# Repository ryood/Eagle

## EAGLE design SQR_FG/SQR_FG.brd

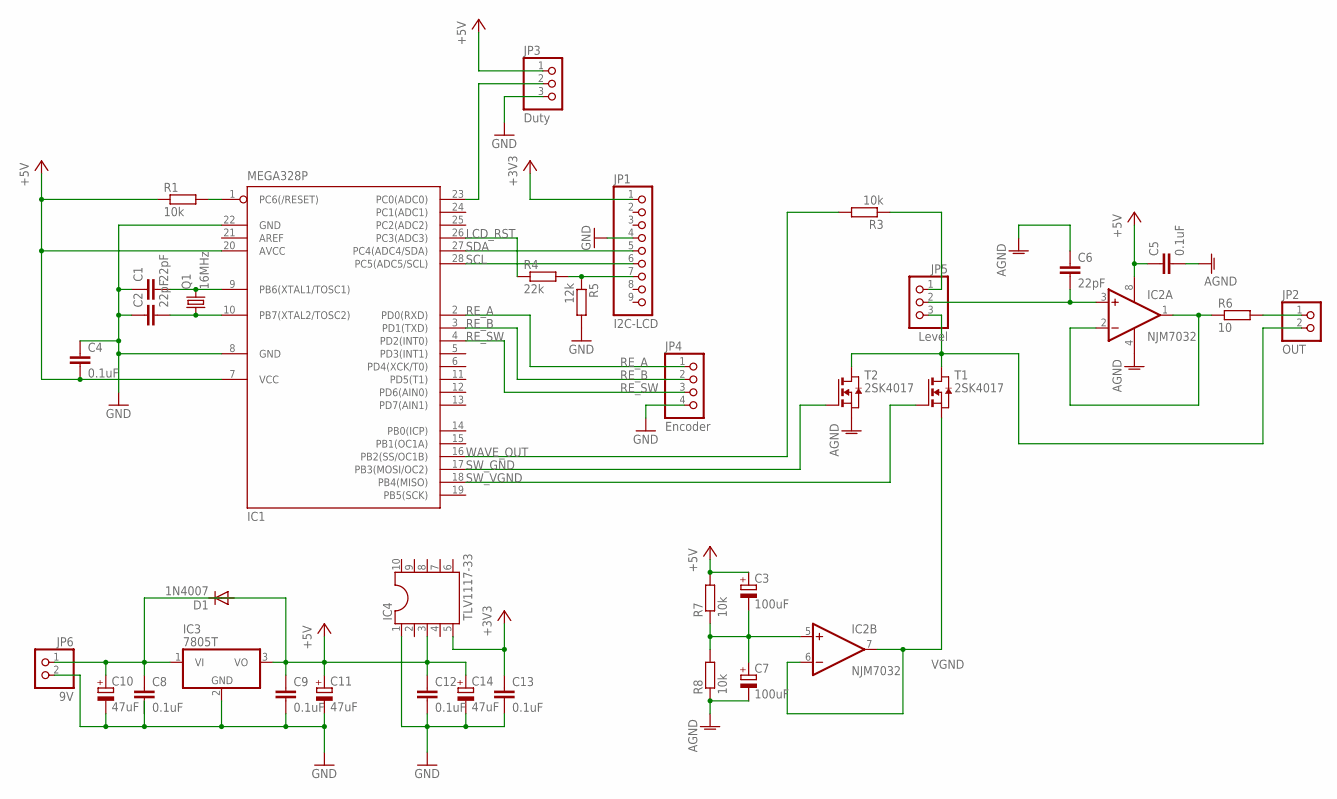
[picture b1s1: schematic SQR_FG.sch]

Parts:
C1, C2, C6: 22pF; C025-024X044
C3, C7: 100uF; E2,5-5
C4, C5, C8, C9, C12, C13: 0.1uF; C025-024X044
C10, C11, C14: 47uF; TT2D5L
D1: 1N4007; DO41-10
IC1: MEGA328P; DIL28-3
IC2: NJM7032; DIL08
IC3: 7805T; TO220H
IC4: TLV1117-33; DIL10
JP1: I2C-LCD; 1X09
JP2: OUT; 1X02
JP3: Duty; 1X03
JP4: Encoder; 1X04
JP5: Level; 1X03
JP6: 9V; 1X02
Q1: 16MHz; HC49/S
R1, R3, R7, R8: 10k; 0207/7
R4: 22k; 0207/7
R5: 12k; 0207/7
R6: 10; 0207/7
T1, T2: 2SK4017; E3LINE

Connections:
+3V3: C13.1, IC4.5, JP1.1
+5V: C3.+, C4.2, C5.1, C8.1, C9.1, C10.+, C11.+, C12.1, C14.+, IC1.7 (VCC), IC1.20 (AVCC), IC2.8 (V+), IC3.1 (VI), IC3.3 (VO), IC4.3, JP3.1, JP6.1, R1.1, R7.2
AGND: C5.2, C6.1, C7.-, IC2.4 (V-), R8.1, T2.3 (S)
GND: C1.1, C2.1, C4.1, C8.2, C9.2, C10.-, C11.-, C12.2, C13.2, C14.-, IC1.8 (GND), IC1.22 (GND), IC3.2 (GND), IC4.1, JP1.4, JP3.3, JP4.4, JP6.2, R5.2
LCD_RST: IC1.26 (PC3(ADC3)), R4.1
unnamed: C1.2, IC1.9 (PB6(XTAL1/TOSC1)), Q1.2
unnamed: C2.2, IC1.10 (PB7(XTAL2/TOSC2)), Q1.1
unnamed: IC1.1 (PC6(/RESET)), R1.2
unnamed: JP2.2, JP5.3, T1.1 (D), T2.1 (D)
unnamed: JP5.1, R3.1
unnamed: IC1.23 (PC0(ADC0)), JP3.2
unnamed: JP2.1, R6.2
unnamed: C6.2, IC2.3 (+IN), JP5.2
unnamed: IC2.1 (OUT), IC2.2 (-IN), R6.1
unnamed: C3.-, C7.+, IC2.5 (+IN), R7.1, R8.2
RE_A: IC1.2 (PD0(RXD)), JP4.1
RE_B: IC1.3 (PD1(TXD)), JP4.2
RE_SW: IC1.4 (PD2(INT0)), JP4.3
RST: JP1.7, R4.2, R5.1
SCL: IC1.28 (PC5(ADC5/SCL)), JP1.6
SDA: IC1.27 (PC4(ADC4/SDA)), JP1.5
SW_GND: IC1.17 (PB3(MOSI/OC2)), T2.2 (G)
SW_VGND: IC1.18 (PB4(MISO)), T1.2 (G)
VGND: IC2.6 (-IN), IC2.7 (OUT), T1.3 (S)
WAVE_OUT: IC1.16 (PB2(SS/OC1B)), R3.2

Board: 2 copper layers, 35 parts (0 on the bottom side), 25 nets, no tracks yet.

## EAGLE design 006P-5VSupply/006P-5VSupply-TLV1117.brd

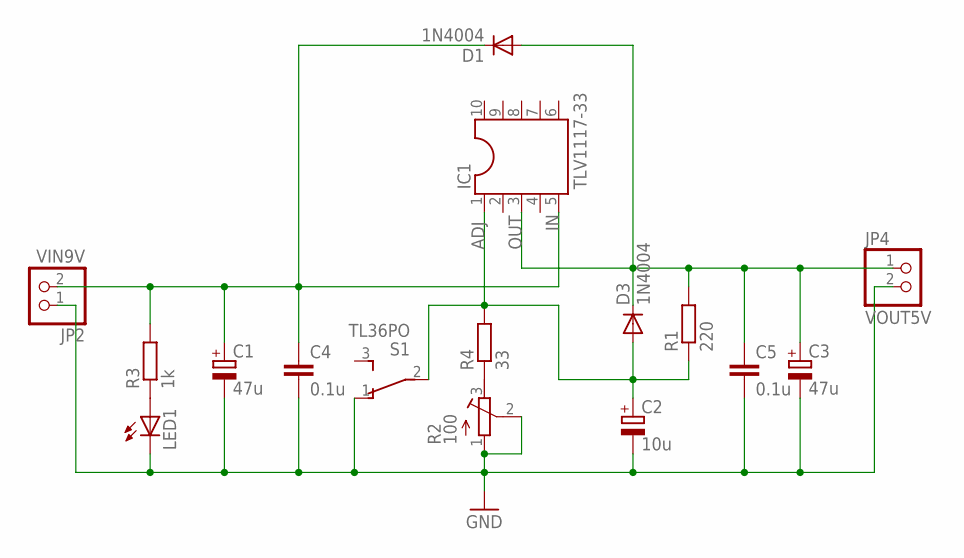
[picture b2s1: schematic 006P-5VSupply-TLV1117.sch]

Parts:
C1, C3: 47u; E2-4
C2: 10u; E2-4
C4, C5: 0.1u; C025-024X044
D1, D3: 1N4004; DO41-10
IC1: TLV1117-33; DIL10
JP2: VIN9V; 1X02
JP4: VOUT5V; 1X02
LED1: LED3MM
R1: 220; 0207/7
R2: 100; RTRIM3339P
R3: 1k; 0207/7
R4: 33; 0207/7
S1: TL36PO; TL3XPO

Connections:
ADJ: C2.+, D3.A, IC1.1, R1.1, R4.2, S1.2
GND: C1.-, C2.-, C3.-, C4.2, C5.2, JP2.1, JP4.2, LED1.K (C), R2.1 (A), R2.2 (S), S1.1 (O)
IN: C1.+, C4.1, D1.C, IC1.5, JP2.2, R3.2
unnamed: R2.3 (E), R4.1
unnamed: LED1.A, R3.1
OUT: C3.+, C5.1, D1.A, D3.C, IC1.3, JP4.1, R1.2

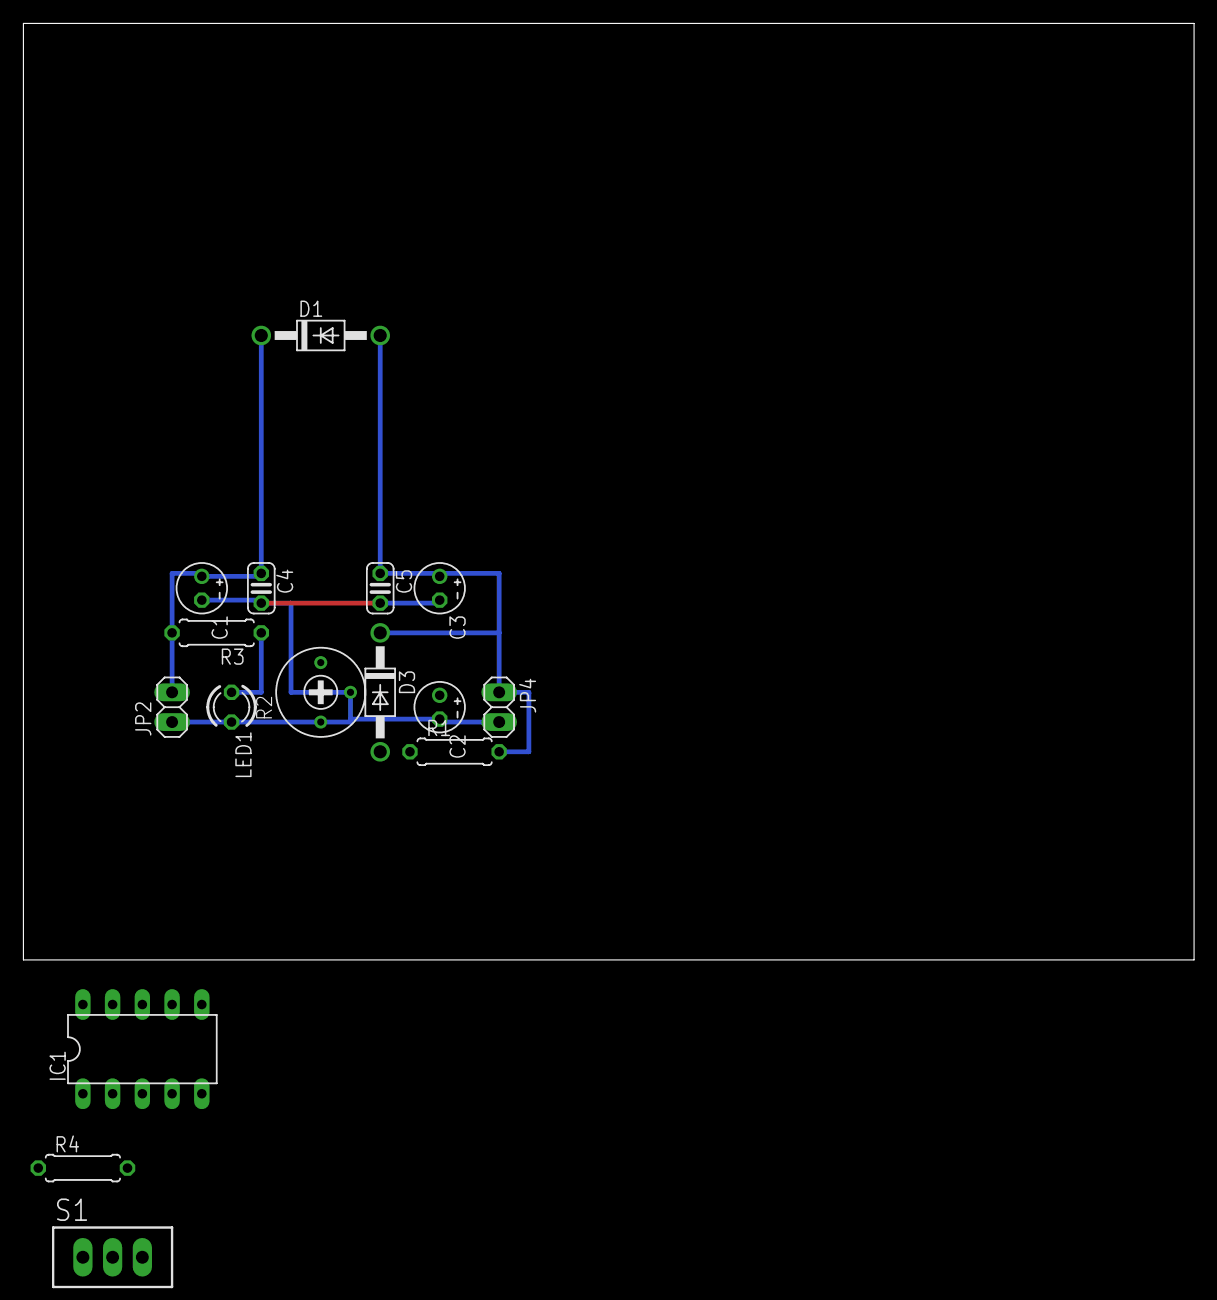
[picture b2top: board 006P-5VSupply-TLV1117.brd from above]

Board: 2 copper layers, 100.0 x 80.0 mm, 16 parts (0 on the bottom side), 6 nets.

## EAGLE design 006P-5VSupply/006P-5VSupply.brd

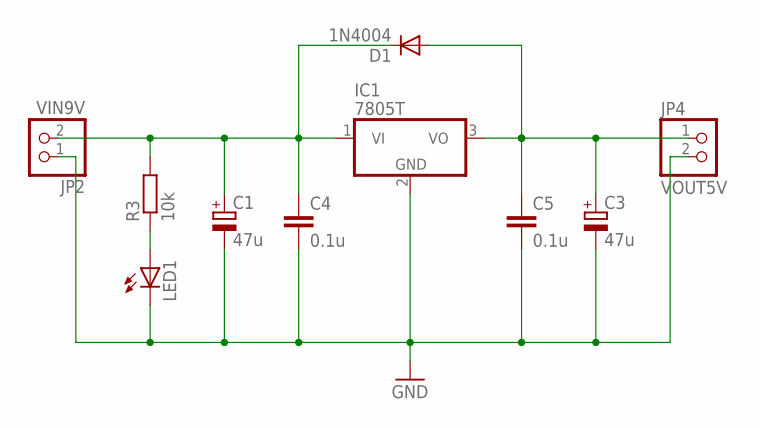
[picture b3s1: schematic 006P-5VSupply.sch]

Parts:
C1, C3: 47u; E2-4
C4, C5: 0.1u; C025-024X044
D1: 1N4004; DO41-10
IC1: 7805T; TO220H
JP2: VIN9V; 1X02
JP4: VOUT5V; 1X02
LED1: LED3MM
R3: 10k; 0207/7

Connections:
GND: C1.-, C3.-, C4.2, C5.2, IC1.2 (GND), JP2.1, JP4.2, LED1.K (C)
unnamed: C3.+, C5.1, D1.A, IC1.3 (VO), JP4.1
unnamed: C1.+, C4.1, D1.C, IC1.1 (VI), JP2.2, R3.2
unnamed: LED1.A, R3.1

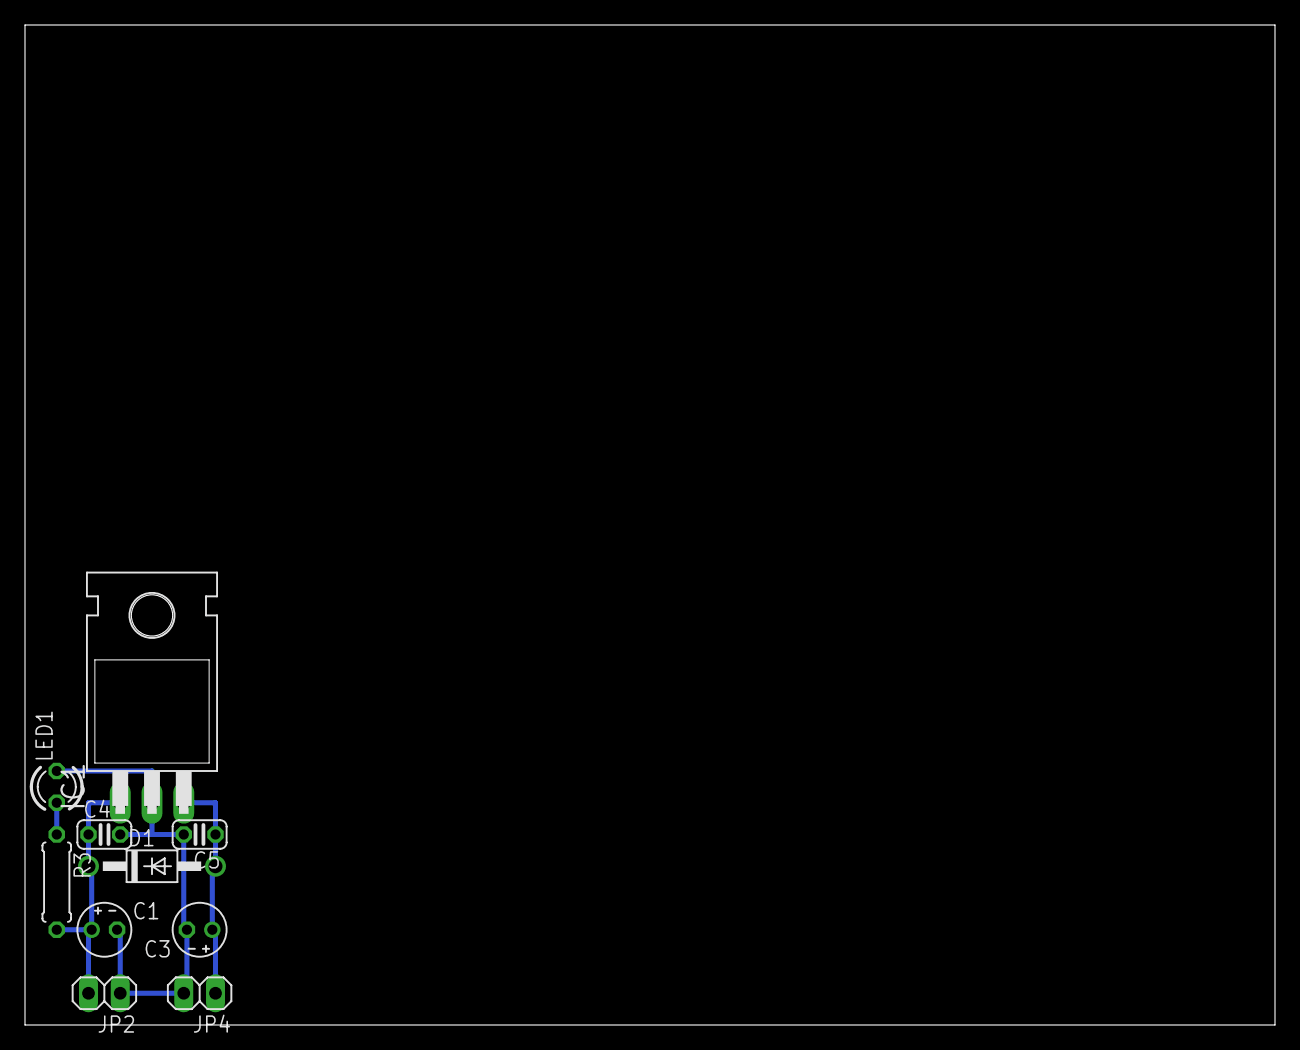
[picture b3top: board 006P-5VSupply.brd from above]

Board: 2 copper layers, 100.0 x 80.0 mm, 10 parts (0 on the bottom side), 4 nets.

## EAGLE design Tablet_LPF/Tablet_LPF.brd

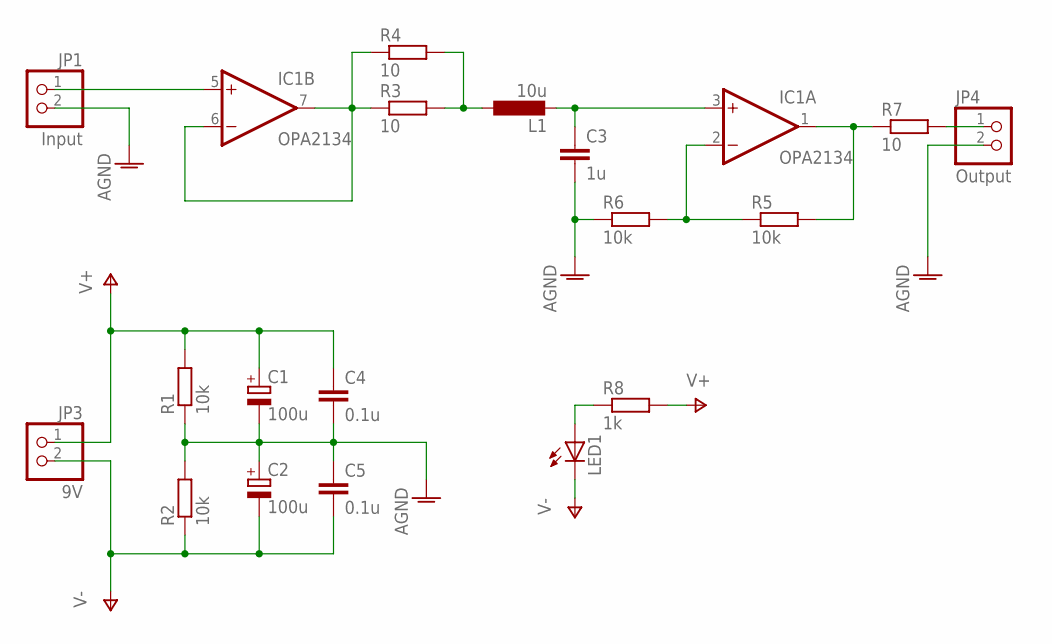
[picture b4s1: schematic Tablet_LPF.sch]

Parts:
C1, C2: 100u; E2,5-7
C3: 1u; C050-045X075
C4, C5: 0.1u; C025-024X044
IC1: OPA2134; DIL08
JP1: Input; 1X02
JP3: 9V; 1X02
JP4: Output; 1X02
L1: 10u; 6000-XXXX-RC
LED1: LED3MM
R1, R2, R5, R6: 10k; 0207/7
R3, R4, R7: 10; 0207/7
R8: 1k; 0207/7

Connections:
AGND: C1.-, C2.+, C3.2, C4.2, C5.1, JP1.2, JP4.2, R1.1, R2.2, R6.1
unnamed: LED1.A, R8.1
unnamed: IC1.5 (+IN), JP1.1
unnamed: IC1.6 (-IN), IC1.7 (OUT), R3.1, R4.1
unnamed: L1.1, R3.2, R4.2
unnamed: C3.1, IC1.3 (+IN), L1.2
unnamed: JP4.1, R7.2
unnamed: IC1.1 (OUT), R5.2, R7.1
unnamed: IC1.2 (-IN), R5.1, R6.2
V+: C1.+, C4.1, IC1.8 (V+), JP3.1, R1.2, R8.2
V-: C2.-, C5.2, IC1.4 (V-), JP3.2, LED1.K (C), R2.1

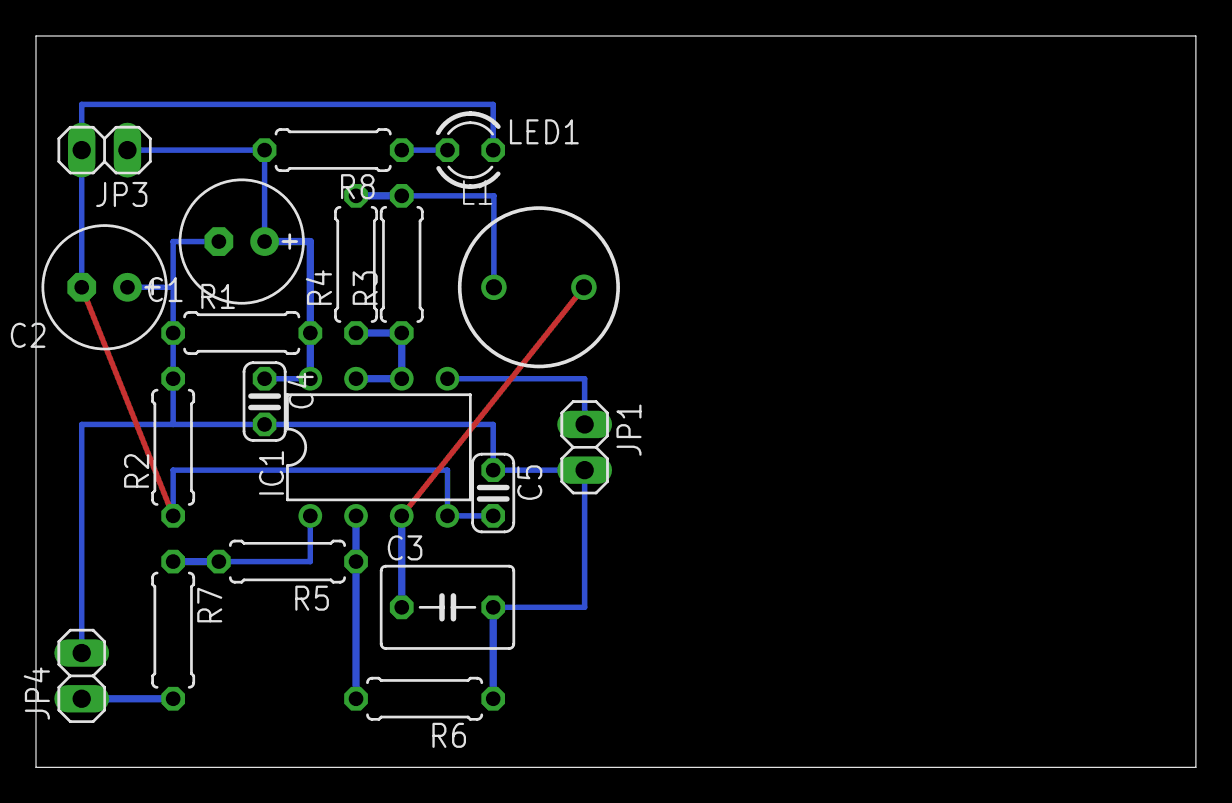
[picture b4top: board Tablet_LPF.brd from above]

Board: 2 copper layers, 64.4 x 40.6 mm, 19 parts (0 on the bottom side), 11 nets.

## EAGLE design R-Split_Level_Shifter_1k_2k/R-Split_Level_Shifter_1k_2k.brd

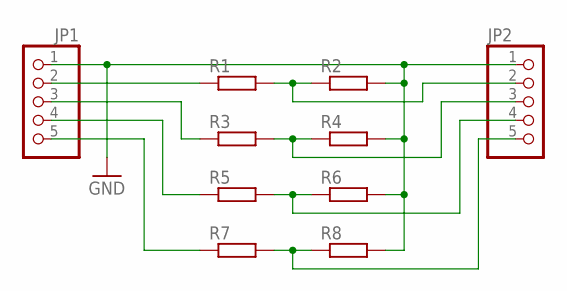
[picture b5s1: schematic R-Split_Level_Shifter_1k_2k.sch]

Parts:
JP1, JP2: PINHD-1X5; 1X05
R1, R2, R3, R4, R5, R6, R7, R8: R-EU_0207/7; 0207/7

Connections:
GND: JP1.1, JP2.1, R2.2, R4.2, R6.2, R8.2
unnamed: JP1.2, R1.1
unnamed: JP2.2, R1.2, R2.1
unnamed: JP1.3, R3.1
unnamed: JP2.3, R3.2, R4.1
unnamed: JP1.4, R5.1
unnamed: JP1.5, R7.1
unnamed: JP2.4, R5.2, R6.1
unnamed: JP2.5, R7.2, R8.1

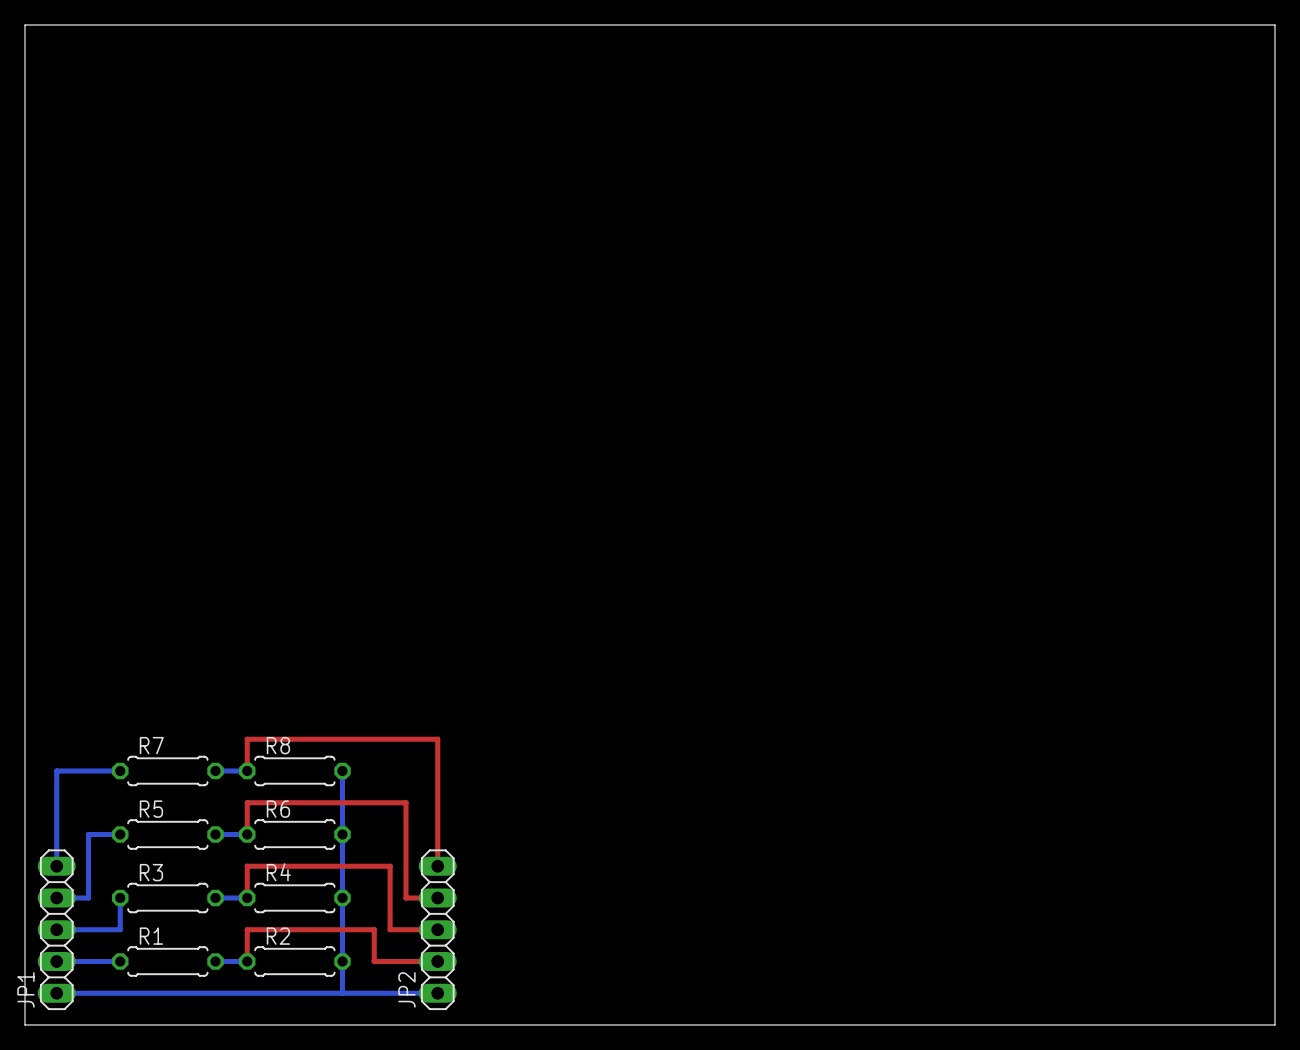
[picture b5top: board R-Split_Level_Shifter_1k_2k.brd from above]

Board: 2 copper layers, 100.0 x 80.0 mm, 10 parts (0 on the bottom side), 9 nets.

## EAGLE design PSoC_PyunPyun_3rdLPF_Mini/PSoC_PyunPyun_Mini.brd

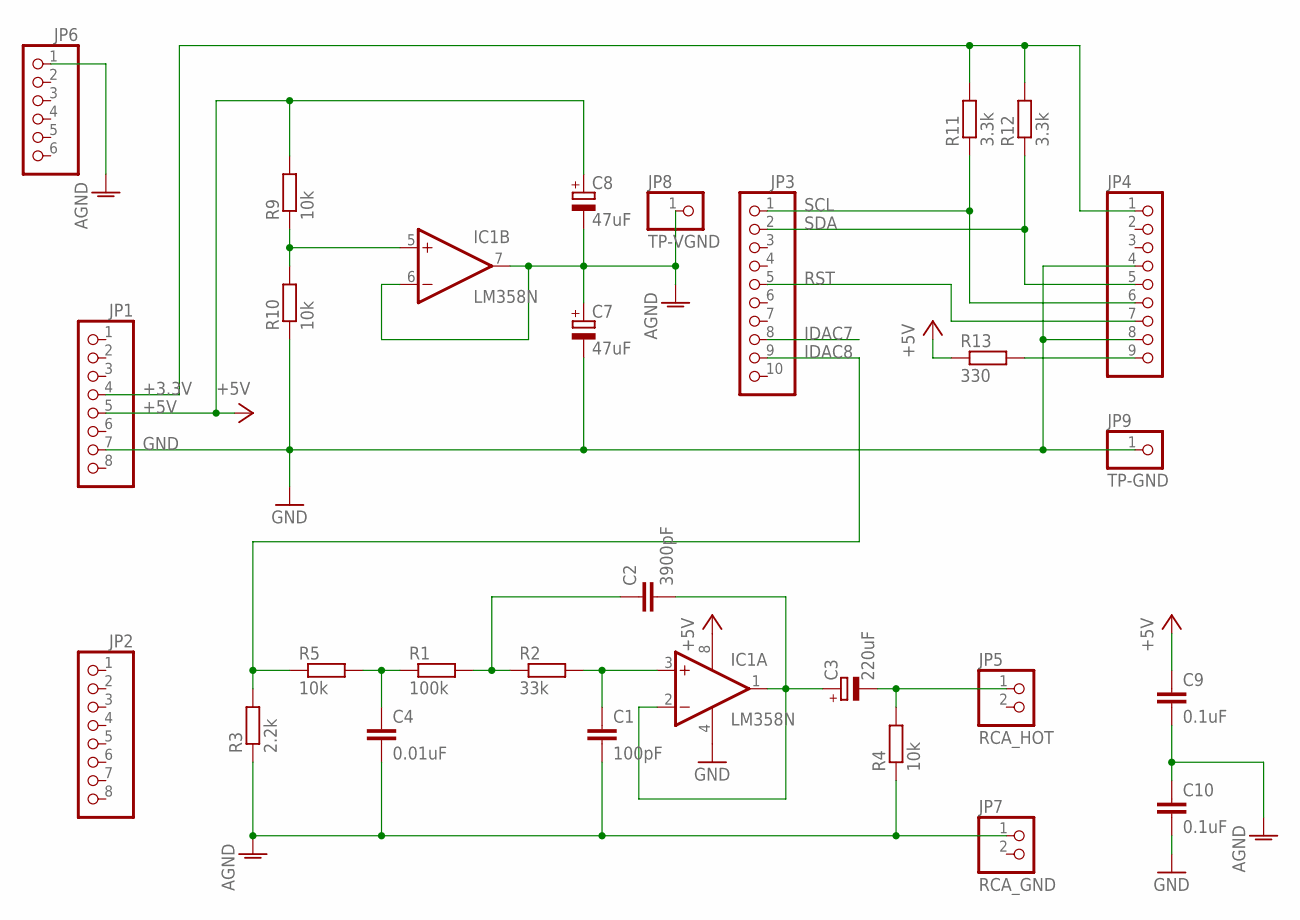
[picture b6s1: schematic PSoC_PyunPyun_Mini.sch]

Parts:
C1: 100pF; C050-024X044
C2: 3900pF; C050-024X044
C3: 220uF; E5-8,5
C4: 0.01uF; C050-024X044
C7, C8: 47uF; E5-5
C9, C10: 0.1uF; C050-024X044
IC1: LM358N; DIL08
JP1, JP2: PINHD-1X8; 1X08
JP3: PINHD-1X10; 1X10
JP4: PINHD-1X9; 1X09
JP5: RCA_HOT; 1X02
JP6: PINHD-1X6; 1X06
JP7: RCA_GND; 1X02
JP8: TP-VGND; 1X01
JP9: TP-GND; 1X01
R1: 100k; 0207/7
R2: 33k; 0207/7
R3: 2.2k; 0207/7
R4, R5, R9, R10: 10k; 0207/7
R11, R12: 3.3k; 0207/7
R13: 330; 0207/7

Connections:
+3.3V: JP1.4, JP4.1, R11.2, R12.2
+5V: C8.+, C9.1, IC1.8 (V+), JP1.5, R9.2, R13.1
AGND: C1.2, C4.2, C7.+, C8.-, C9.2, C10.1, IC1.6 (-IN), IC1.7 (OUT), JP6.1, JP7.1, JP8.1, R3.1, R4.1
GND: C7.-, C10.2, IC1.4 (V-), JP1.7, JP4.4, JP4.8, JP9.1, R10.1
IDAC7: JP3.8
IDAC8: JP3.9, R3.2, R5.1
unnamed: C2.1, R1.2, R2.1
unnamed: C4.1, R1.1, R5.2
unnamed: C1.1, IC1.3 (+IN), R2.2
unnamed: C2.2, C3.+, IC1.1 (OUT), IC1.2 (-IN)
unnamed: JP4.9, R13.2
unnamed: C3.-, JP5.1, R4.2
unnamed: IC1.5 (+IN), R9.1, R10.2
RST: JP3.5, JP4.7
SCL: JP3.1, JP4.6, R11.1
SDA: JP3.2, JP4.5, R12.1

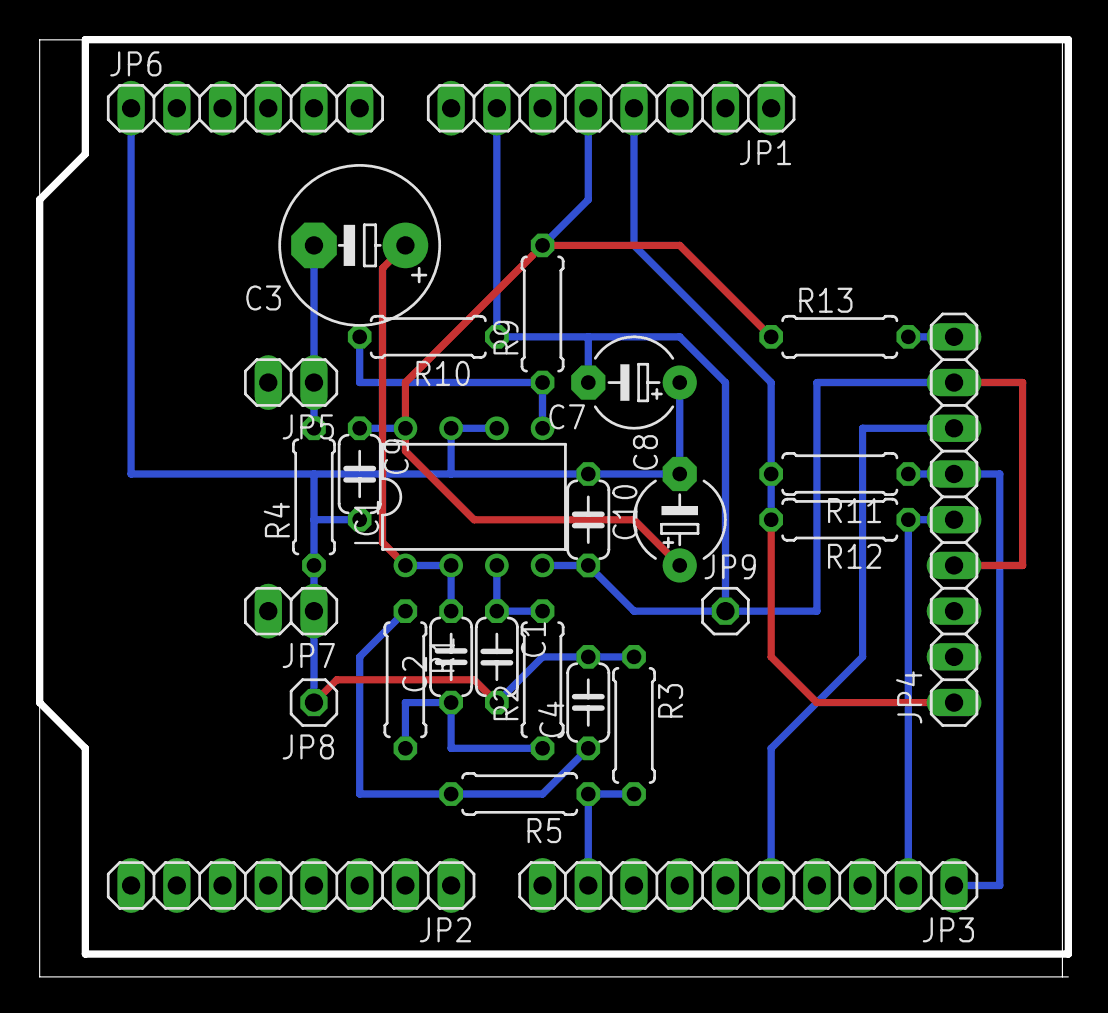
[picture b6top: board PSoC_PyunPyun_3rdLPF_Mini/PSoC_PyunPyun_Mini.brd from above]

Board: 2 copper layers, 57.1 x 52.1 mm, 28 parts (0 on the bottom side), 15 nets.

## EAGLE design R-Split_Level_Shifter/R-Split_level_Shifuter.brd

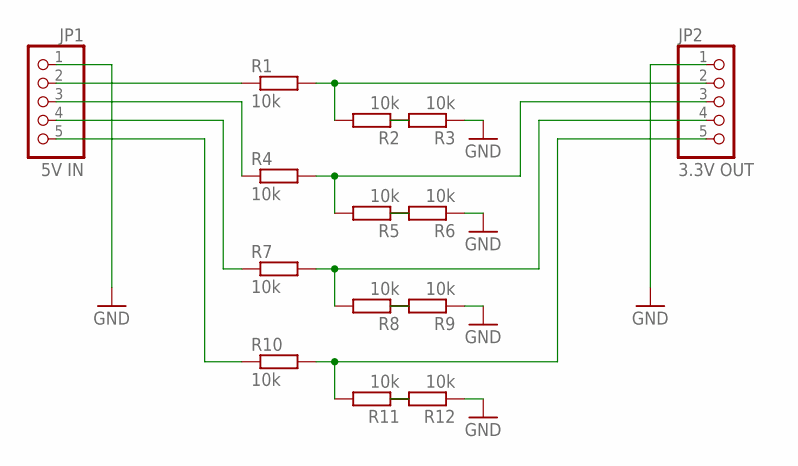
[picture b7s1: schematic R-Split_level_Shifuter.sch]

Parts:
JP1: 5V IN; 1X05
JP2: 3.3V OUT; 1X05
R1, R2, R3, R4, R5, R6, R7, R8, R9, R10, R11, R12: 10k; 0207/7

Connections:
GND: JP1.1, JP2.1, R3.1, R6.1, R9.1, R12.1
unnamed: R2.1, R3.2
unnamed: JP1.2, R1.1
unnamed: JP2.2, R1.2, R2.2
unnamed: JP2.4, R7.2, R8.2
unnamed: JP2.3, R4.2, R5.2
unnamed: R5.1, R6.2
unnamed: R8.1, R9.2
unnamed: JP2.5, R10.2, R11.2
unnamed: R11.1, R12.2
unnamed: JP1.3, R4.1
unnamed: JP1.4, R7.1
unnamed: JP1.5, R10.1

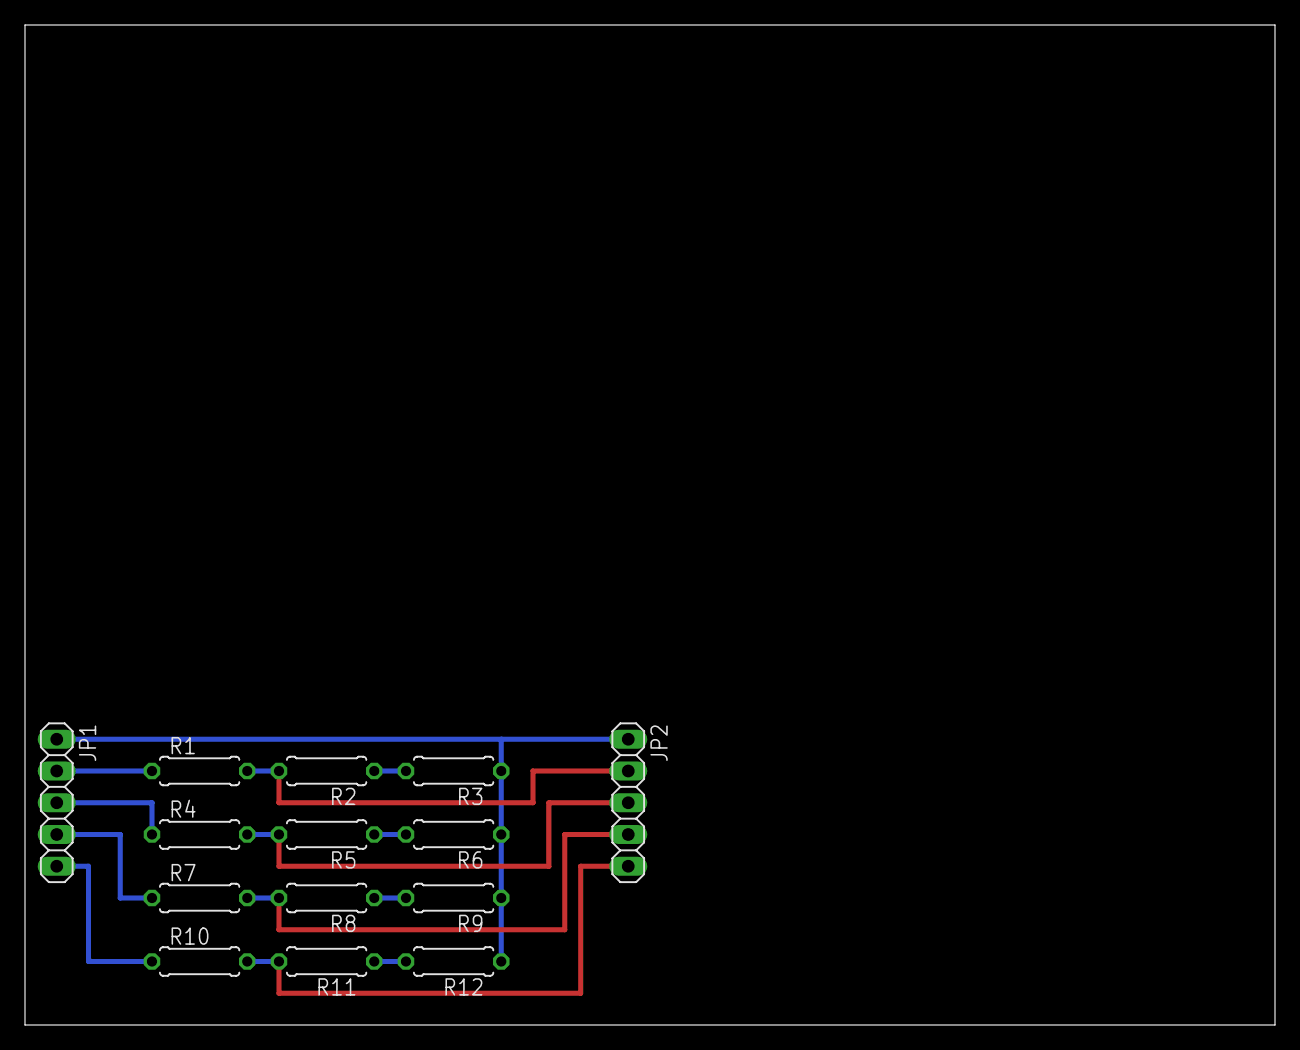
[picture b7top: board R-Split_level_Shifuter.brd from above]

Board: 2 copper layers, 100.0 x 80.0 mm, 14 parts (0 on the bottom side), 13 nets.

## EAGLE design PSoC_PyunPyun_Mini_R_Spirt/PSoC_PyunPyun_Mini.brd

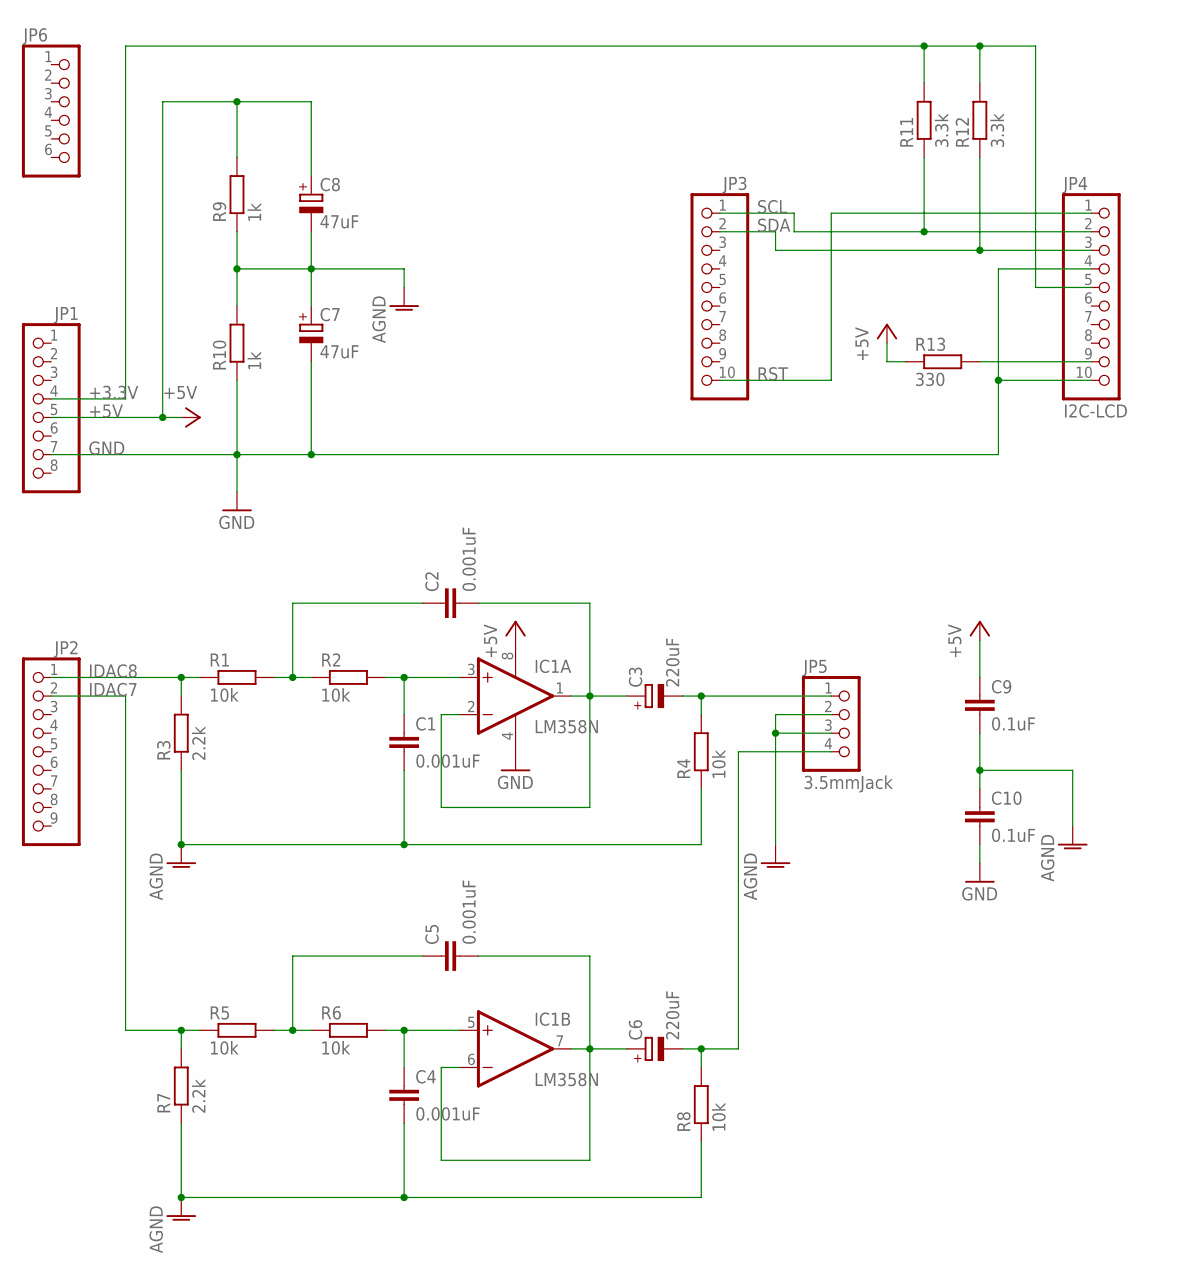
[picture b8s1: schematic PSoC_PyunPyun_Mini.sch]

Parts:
C1, C2, C4, C5: 0.001uF; C050-024X044
C3, C6: 220uF; E5-8,5
C7, C8: 47uF; E5-5
C9, C10: 0.1uF; C050-024X044
IC1: LM358N; DIL08
JP1: PINHD-1X8; 1X08
JP2: PINHD-1X9; 1X09
JP3: PINHD-1X10; 1X10
JP4: I2C-LCD; 1X10
JP5: 3.5mmJack; 1X04
JP6: PINHD-1X6; 1X06
R1, R2, R4, R5, R6, R8: 10k; 0207/7
R3, R7: 2.2k; 0207/7
R9, R10: 1k; 0207/7
R11, R12: 3.3k; 0207/7
R13: 330; 0207/7

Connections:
+3.3V: JP1.4, JP4.5, R11.2, R12.2
+5V: C8.+, C9.1, IC1.8 (V+), JP1.5, R9.2, R13.1
AGND: C1.2, C4.2, C7.+, C8.-, C9.2, C10.1, JP5.2, JP5.3, R3.1, R4.1, R7.1, R8.1, R9.1, R10.2
GND: C7.-, C10.2, IC1.4 (V-), JP1.7, JP4.4, JP4.10, R10.1
IDAC7: JP2.2, R5.1, R7.2
IDAC8: JP2.1, R1.1, R3.2
unnamed: C2.1, R1.2, R2.1
unnamed: C5.1, R5.2, R6.1
unnamed: C1.1, IC1.3 (+IN), R2.2
unnamed: C2.2, C3.+, IC1.1 (OUT), IC1.2 (-IN)
unnamed: JP4.9, R13.2
unnamed: C4.1, IC1.5 (+IN), R6.2
unnamed: C3.-, JP5.1, R4.2
unnamed: C5.2, C6.+, IC1.6 (-IN), IC1.7 (OUT)
unnamed: C6.-, JP5.4, R8.2
RST: JP3.10, JP4.1
SCL: JP3.1, JP4.2, R11.1
SDA: JP3.2, JP4.3, R12.1

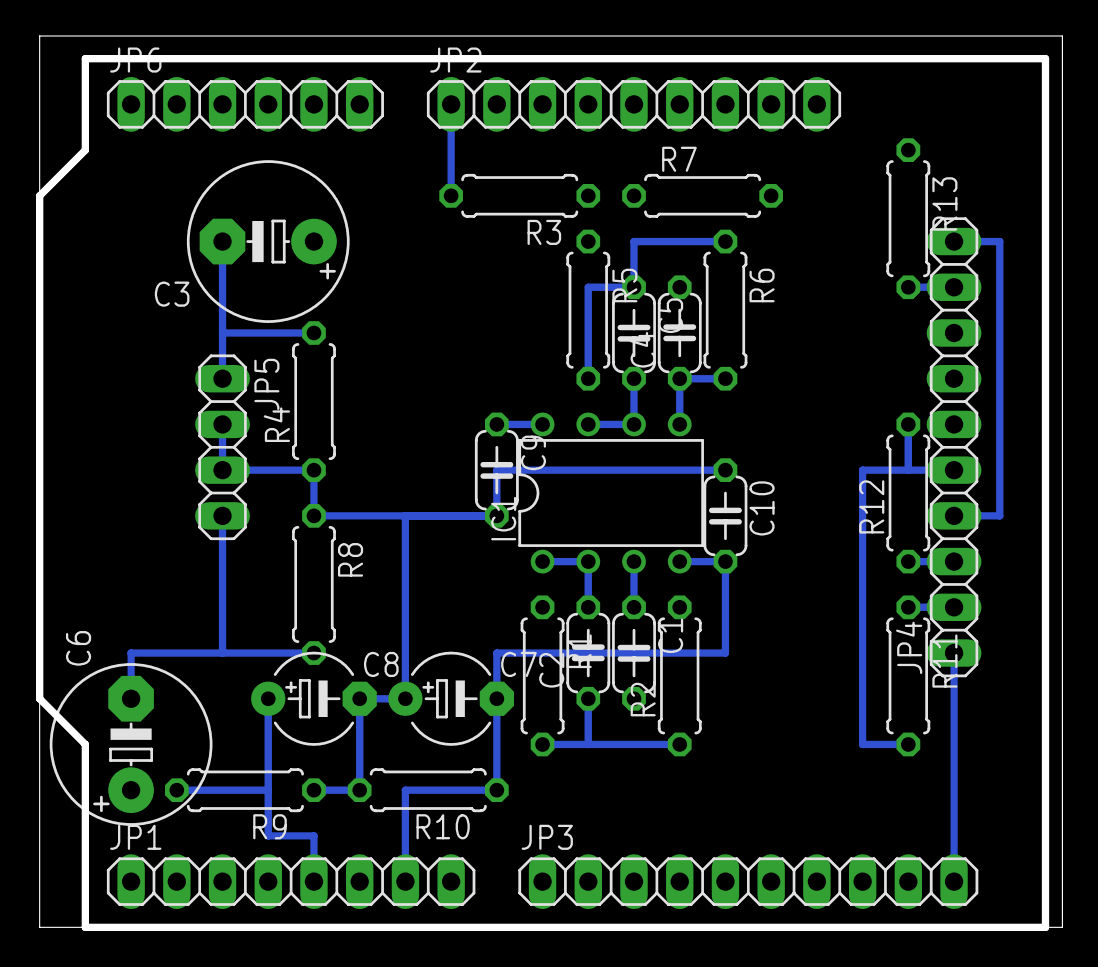
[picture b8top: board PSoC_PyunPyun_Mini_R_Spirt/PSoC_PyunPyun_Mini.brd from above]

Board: 2 copper layers, 56.8 x 49.5 mm, 30 parts (0 on the bottom side), 18 nets.

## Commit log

2015-02-26 PSoC Pyun Pyun miniの基板図を作成
2015-02-26 PSoC Pyun Pyunの基板図を作成
2015-02-27 PSoC_PyunPyun_Min Projectを追加
2015-02-27 PSoC_PyunPyun_Mini_R_Spritを追加
2015-02-27 PSoC_PyunPyun_Mini ボード図変更 LCDの位置を上にずらした
2015-03-04 PSoC PyunPyun Mini 基板設計図変更
2015-03-06 PSoC_PyunPyun_Mini変更
2015-03-06 PSoC_PyunPyun_3rdLPF_Mini追加
2015-03-09 PSoC_PyunPyun_3rdLPF_Mini 回路図修正
2015-03-11 PSoC_PyunPyun_3rdLPF 回路図修正
2015-03-14 PSoC_Pyun_Pyun_Mini 回路図、基板図修正
2015-03-18 Add R-Split_level_Shifter
2015-03-19 PSoC_Pyun_Pyun_3rdLPF_Mini: Change LCD to aitendo
2015-04-03 Add Tablet LPF Project
2015-04-10 Change Tablet_LPF Board
2015-05-02 ADD 006P-5VSupply, SQR_FG
2015-05-04 SQR_FG MOS-FET Switch
2015-05-04 Add 006P-5VSupply-TLV1117-33
2015-05-04 SQR_FG Add 2nd VCVS LPF
2015-05-04 SQR_FG Bypass by C
2015-05-07 SQR_FG.sch changed
2015-05-09 Update 006P-5VSupply Project
2015-05-09 SQR_FG Schematic Updated
2015-05-17 SQR_FG: デジタル部と出力部に基板を分割
